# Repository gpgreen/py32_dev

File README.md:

# py32_dev

KiCad design for a ARM Cortex-M0+ development board. The MCU is a Puya
PY32 Series. The specific part is PY032F030K18T6. This can run at a
maximum of 48 MHz, and has 8 kbyte SRAM and 64 kbyte Flash. A USB C
connector provides 5V power only to the development board. The board
must be programmed with a debugger. External crystals are laid out for
the MCU to use a 32.768 kHz low speed crystal or a 24 MHz high speed
crystal. There is an onboard LDO that provides 500mA of power at
3.3V. A resettable fuse protects the USB port from a short. There is
an LED and push button connected to 2 of the GPIO pins. The value of
the BOOT0 pin can be set to ground or 3.3V permanently via the solder
bridge. A jumper can be used on the pin rails in lieue of the solder
bridge. All available GPIO pins are routed to the 2 18pin headers.

## Changes

- Rev B
  Moved resettable fuse away from USB C connector, giving more room to resolder
  connector pins.

- Rev A
  Original

## Firmware

Example firmware that blinks the LED. When the user pushbutton is pressed,
the frequency of the LED blink will change.

https://github.com/gpgreen/py32-dev-blink

## Boot configuration

To boot from main flash [0x0800_0000]
  Connect J2-4 to J2-5 (or) solder JP5-1 to center post

To boot from System mem [0x1FFF_0000], or Embedded SRAM [0x2000_0000]
  Connect J2-4 to J2-3 (or) solder JP6-3 to center post

There is an embedded boot loader, programmed in production, in the system memory
block. See the reference manual 3.6.2.

## PIN JUMPER SIGNAL ASSIGNMENT
```
                    +-----+
            +--------------------+
            |J3     |     |    J2|
        VDD-|1      +-----+     1|-GND
        GND-|2                  2|-GND
       +3.3-|3                  3|-+3.3
[RESET] PF2-|4                  4|-PF4 [BOOT0_PRE]
[SWCLK]PA14-|5                  5|-GND
[SWDIO]PA13-|6                  6|-GND
        GND-|7       RST        7|-GND
        PF3-|8       +-+        8|-GND
        PA0-|9       |O|        9|-GND
        PA1-|10      +-+       10|-PB7
        PA2-|11                11|-PB6
        PA3-|12                12|-PB5
        PA4-|13                13|-PB4
        PA6-|14                14|-PB3
        PA6-|15   UPB          15|-PA15
        PA7-|16   +-+          16|-PA12 [USER LED - GREEN]
        PB0-|17   |O|          17|-PA11 [USER PUSHBUTTON]
        PB1-|18   +-+          18|-PA8
            |                    |
            +--------------------+
```
## Connections to JTAG

From a 20pin JTAG connector, run wires to the following pins to connect a debugger:

VTRef 1  <-> J3-3
SWDIO 7  <-> J3-6
SWCLK 9  <-> J3-5
RESET 15 <-> J3-4
5V    19 <-> NC
GND   4  <-> J3-2
GND   20 <-> J3-7

## Running SEGGER JLink

Run the JLink GDB server via the following:
```
JLinkGDBServer -if SWD -JLinkDevicesXMLPath ~/.config/SEGGER/JLinkDevices/Puya/PY32/JLinkDevices.xml -device PY32F030xx8
```

GDB can be connected via the following:
```
gdb-multiarch --command=jlink-py32.gdb target/thumbv6m/debug/blink-py32
```

## Links
- [Puya PY32 Series](https://www.puyasemi.com/cpzx3/info_271_aid_247_kid_246.html)
- [Software template for PY32 Series by Jay Carlson](https://github.com/jaydcarlson/py32-template)
- [Fork of template for these boards](https://github.com/gpgreen/py32-dev-blink)
- [Tech documentation for py32f030](https://www.puyasemi.com/uploadfiles/2022/11/PY-MCU%E8%B5%84%E6%96%99-20221117.rar)

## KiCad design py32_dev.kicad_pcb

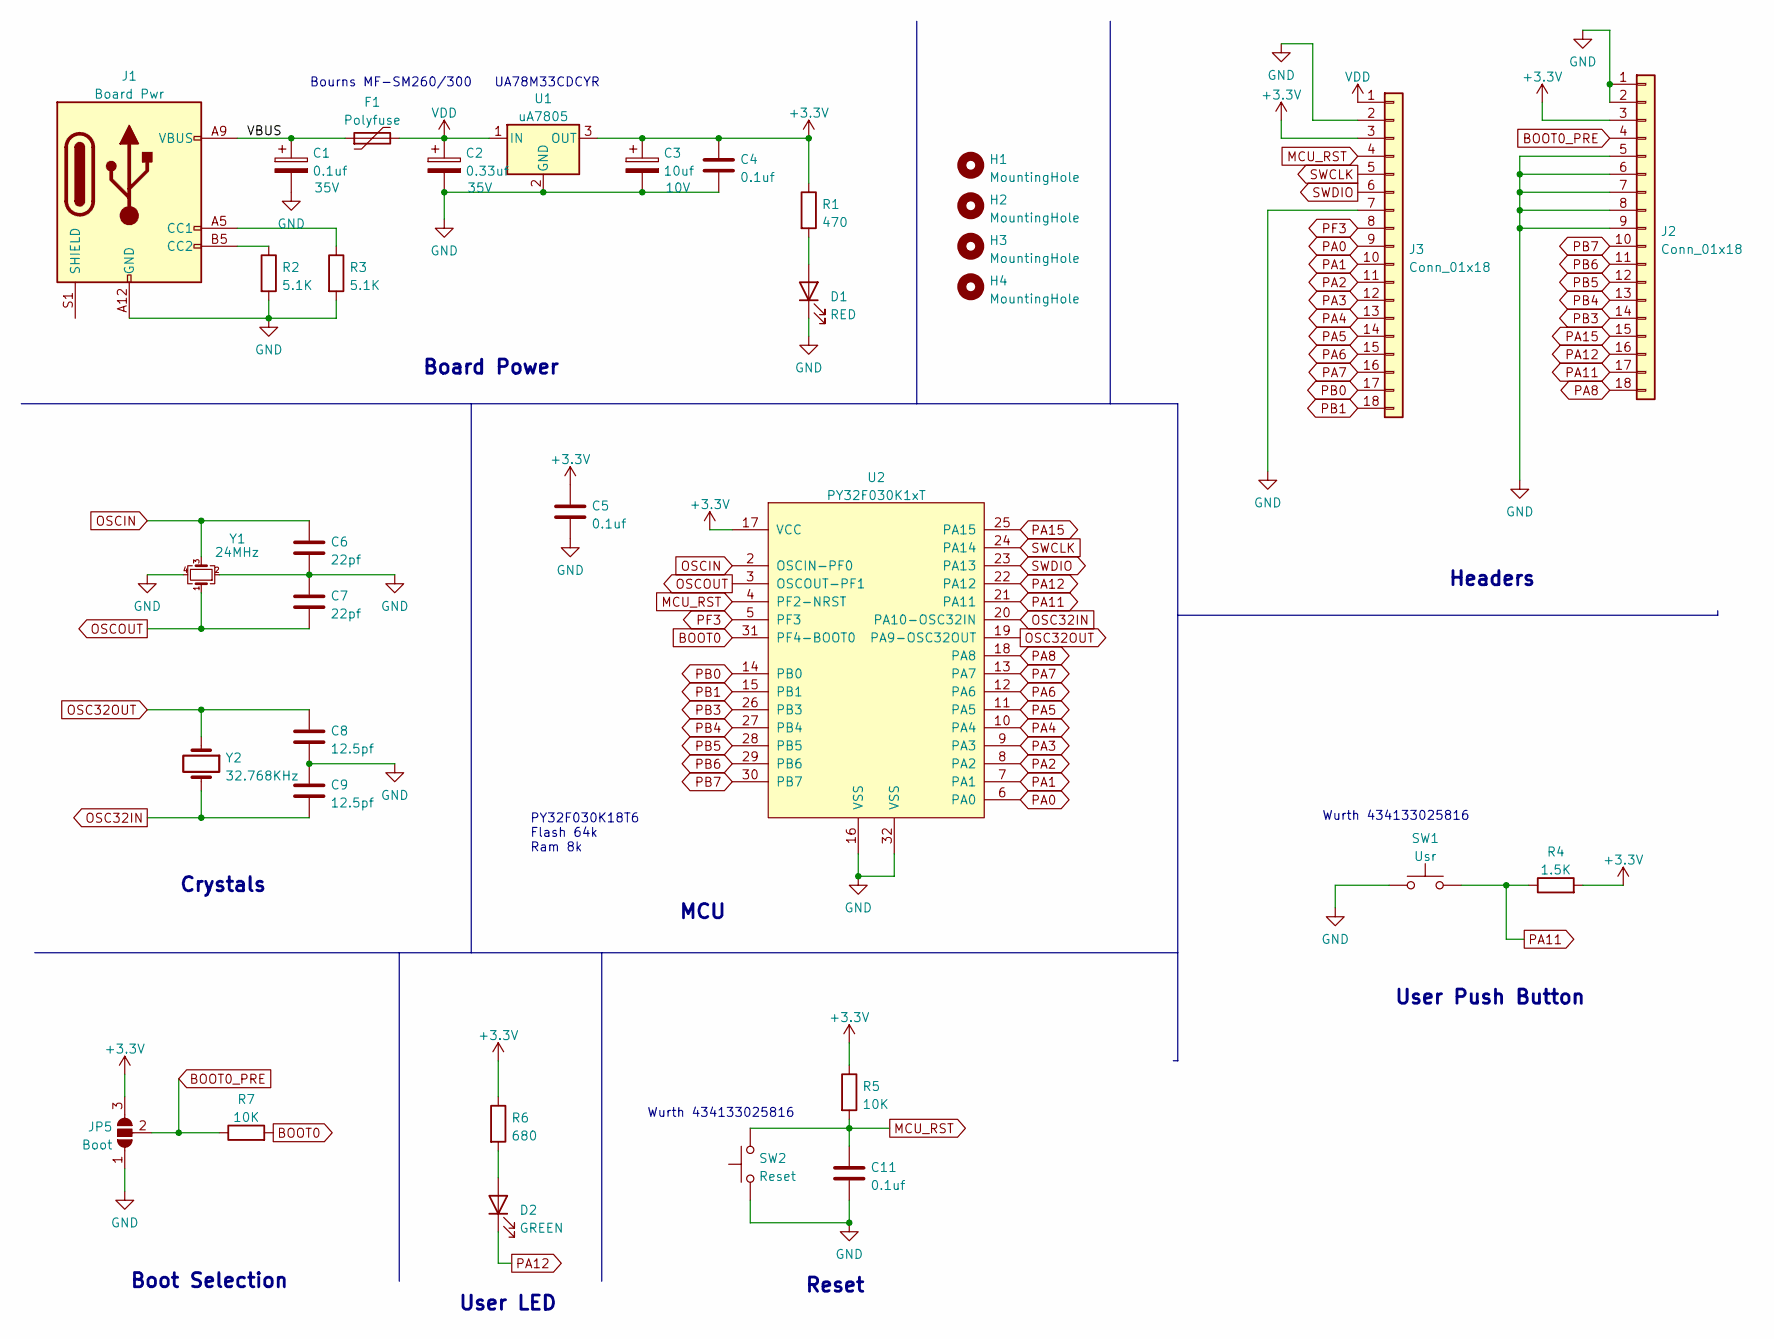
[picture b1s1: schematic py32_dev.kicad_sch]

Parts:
C1: 0.1uf; CP_EIA-3216-18_Kemet-A_Pad1.58x1.35mm_HandSolder; Voltage 35V
C2: 0.33uf; CP_EIA-3216-18_Kemet-A_Pad1.58x1.35mm_HandSolder; Voltage 35V
C3: 10uf; CP_EIA-3216-18_Kemet-A_Pad1.58x1.35mm_HandSolder; Voltage 10V
C4, C5, C11: 0.1uf; C_0603_1608Metric
C6, C7: 22pf; C_0603_1608Metric
C8, C9: 12.5pf; C_0603_1608Metric
D1: RED; D_0603_1608Metric
D2: GREEN; D_0603_1608Metric
F1: Polyfuse; Fuse_Bourns_MF-SM_7.98x5.44mm
H1, H2, H3, H4: MountingHole; MountingHole_2.5mm_Pad
J1: Board Pwr; SHOUHAN TYPE-C 6P
J2, J3: Conn_01x18; PinHeader_1x18_P2.54mm_Vertical
JP5: Boot; SolderJumper-3_P1.3mm_Open_Pad1.0x1.5mm_NumberLabels
R1: 470; R_0603_1608Metric
R2, R3: 5.1K; R_0603_1608Metric
R4: 1.5K; R_0603_1608Metric
R5, R7: 10K; R_0603_1608Metric
R6: 680; R_0603_1608Metric
SW1: Usr; SW_Push_1P1T_NO_Vertical_Wuerth_434133025816
SW2: Reset; SW_Push_1P1T_NO_Vertical_Wuerth_434133025816
U1: uA7805; SOT-223-3_TabPin2
U2: PY32F030K1xT; LQFP-32_7x7mm_P0.8mm
Y1: 24MHz; Crystal_SMD_TXC_7M-4Pin_3.2x2.5mm
Y2: 32.768KHz; Crystal_DS15_D1.5mm_L5.0mm_Horizontal

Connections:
+3.3V: C3.1, C4.1, C5.1, J2.3, J3.3, JP5.3 (B), R1.1, R4.2, R5.1, R6.1, U1.3 (OUT), U2.17 (VCC)
/VBUS: C1.1, F1.1, J1.A9 (VBUS), J1.B9 (VBUS)
BOOT0: R7.2, U2.31 (PF4-BOOT0)
BOOT0_PRE: J2.4, JP5.2 (C), R7.1
GND: C1.2, C2.2, C3.2, C4.2, C5.2, C6.2, C7.1, C8.2, C9.1, C11.2, D1.1 (K), J1.A12 (GND), J1.B12 (GND), J2.1, J2.2, J2.5, J2.6, J2.7, J2.8, J2.9, J3.2, J3.7, JP5.1 (A), R2.2, R3.2, SW1.1, SW2.1, U1.2 (GND), U2.16 (VSS), U2.32 (VSS), Y1.2, Y1.4
MCU_RST: C11.1, J3.4, R5.2, SW2.2, U2.4 (PF2-NRST)
unnamed: D1.2 (A), R1.2
unnamed: D2.2 (A), R6.2
unnamed: J1.A5 (CC1), R3.1
unnamed: J1.B5 (CC2), R2.1
OSC32IN: C9.2, U2.20 (PA10-OSC32IN), Y2.2
OSC32OUT: C8.1, U2.19 (PA9-OSC32OUT), Y2.1
OSCIN: C6.1, U2.2 (OSCIN-PF0), Y1.3
OSCOUT: C7.2, U2.3 (OSCOUT-PF1), Y1.1
PA0: J3.9, U2.6 (PA0)
PA1: J3.10, U2.7 (PA1)
PA2: J3.11, U2.8 (PA2)
PA3: J3.12, U2.9 (PA3)
PA4: J3.13, U2.10 (PA4)
PA5: J3.14, U2.11 (PA5)
PA6: J3.15, U2.12 (PA6)
PA7: J3.16, U2.13 (PA7)
PA8: J2.18, U2.18 (PA8)
PA11: J2.17, R4.1, SW1.2, U2.21 (PA11)
PA12: D2.1 (K), J2.16, U2.22 (PA12)
PA15: J2.15, U2.25 (PA15)
PB0: J3.17, U2.14 (PB0)
PB1: J3.18, U2.15 (PB1)
PB3: J2.14, U2.26 (PB3)
PB4: J2.13, U2.27 (PB4)
PB5: J2.12, U2.28 (PB5)
PB6: J2.11, U2.29 (PB6)
PB7: J2.10, U2.30 (PB7)
PF3: J3.8, U2.5 (PF3)
SWCLK: J3.5, U2.24 (PA14)
SWDIO: J3.6, U2.23 (PA13)
VDD: C2.1, F1.2, J3.1, U1.1 (IN)

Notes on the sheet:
Bourns MF-SM260/300
Wurth 434133025816
Headers
Boot Selection
Crystals
User Push Button
Reset
UA78M33CDCYR
MCU
PY32F030K18T6 Flash 64k Ram 8k
Board Power
User LED

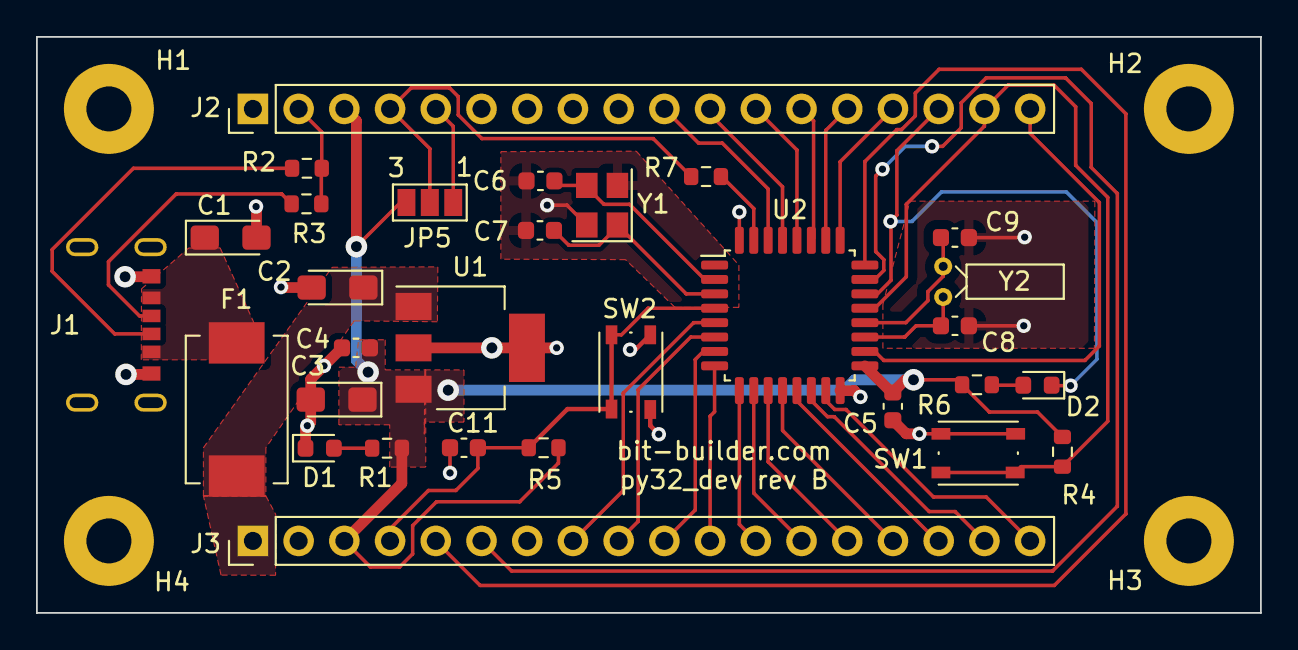
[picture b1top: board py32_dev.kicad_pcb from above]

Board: 2 copper layers, 68.0 x 32.0 mm, 34 parts (0 on the bottom side), 37 nets.

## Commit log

2023-02-17 original design
2023-03-05 Added resistor values R2,R3
2023-03-05 Updated README and schematic pdf
2023-03-05 Updated revision to B
    Moved fuse slightly away from USB connector on the pcb for more room
    to resolder the USB connector pins
2023-03-07 Redid user pushbutton to work correctly
2023-04-03 Removed R4, user PB swap, back to rev A config
    Added link in README to blink firmware repository and puya32 tech docs
2024-04-22 Starting Rev B
2024-10-06 Updated readme with connections for debugger
2024-10-07 Fixed pin labeling errors in README on J2
